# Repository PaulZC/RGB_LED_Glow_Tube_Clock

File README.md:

# RGB LED Glow Tube Clock

A drop-in replacement PCB for one of the popular LED "Nixie" Glow Tube Clocks available through the usual suppliers.

Features:

* ESP32 WROOM processor - uses WiFi to obtain network time from an NTP server
* 60 x WS2812-2020 2mm x 2mm RGB LEDs - to illuminate the engraved acrylic glow tube digits
* VEML7700 ambient light (lux) sensor - the lux can be used to adjust the LED brightness
* USB-C interface - for 5V power and firmware updates

Enjoy!

**_Paul_**

## Licence

Please see [LICENSE.md](./LICENSE.md) for details.

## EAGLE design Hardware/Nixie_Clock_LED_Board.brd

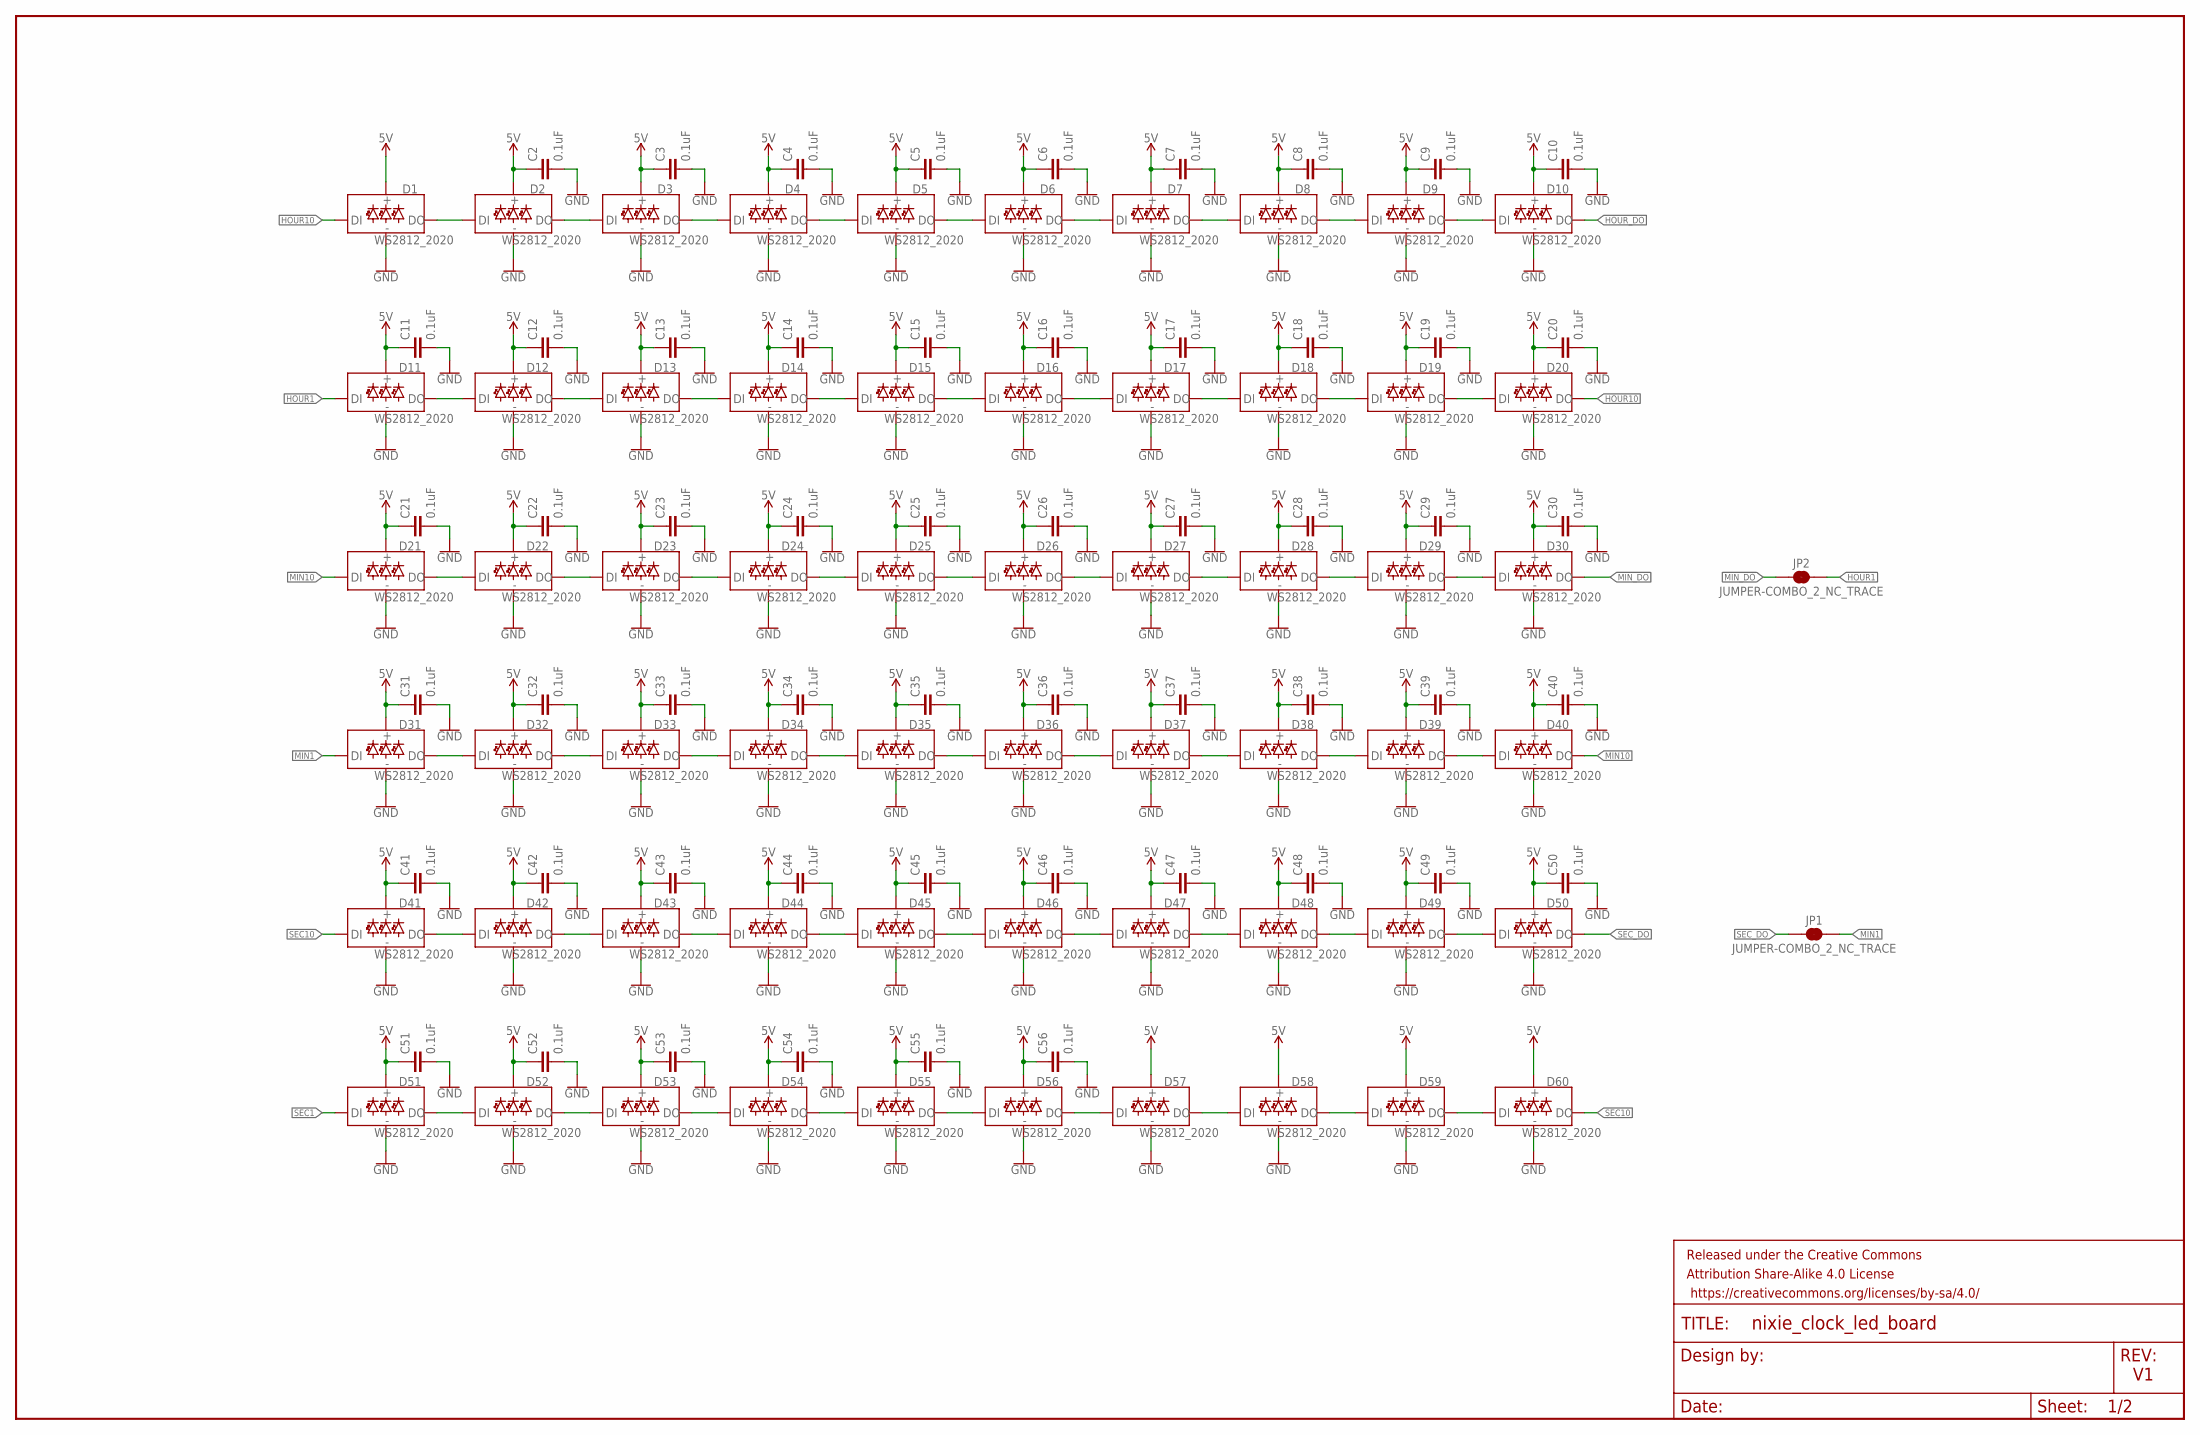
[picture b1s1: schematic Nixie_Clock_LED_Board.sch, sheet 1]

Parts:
C2, C3, C4, C5, C6, C7, C8, C9, C10, C11, C12, C13, C14, C15, C16, C17, C18, C19, C20, C21, C22, C23, C24, C25, C26, C27, C28, C29, C30, C31, C32, C33, C34, C35, C36, C37, C38, C39, C40, C41, C42, C43, C44, C45, C46, C47, C48, C49, C50, C51, C52, C53, C54, C55, C56: 0.1uF; 0603
D1, D2, D3, D4, D5, D6, D7, D8, D9, D10, D11, D12, D13, D14, D15, D16, D17, D18, D19, D20, D21, D22, D23, D24, D25, D26, D27, D28, D29, D30, D31, D32, D33, D34, D35, D36, D37, D38, D39, D40, D41, D42, D43, D44, D45, D46, D47, D48, D49, D50, D51, D52, D53, D54, D55, D56, D57, D58, D59, D60: WS2812_2020; WS2812-2020
FRAME2: FRAME-LEDGER; CREATIVE_COMMONS
JP1, JP2: JUMPER-COMBO_2_NC_TRACE; COMBO-JUMPER_2_NC_TRACE

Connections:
5V: C2.1, C3.1, C4.1, C5.1, C6.1, C7.1, C8.1, C9.1, C10.1, C11.1, C12.1, C13.1, C14.1, C15.1, C16.1, C17.1, C18.1, C19.1, C20.1, C21.1, C22.1, C23.1, C24.1, C25.1, C26.1, C27.1, C28.1, C29.1, C30.1, C31.1, C32.1, C33.1, C34.1, C35.1, C36.1, C37.1, C38.1, C39.1, C40.1, C41.1, C42.1, C43.1, C44.1, C45.1, C46.1, C47.1, C48.1, C49.1, C50.1, C51.1, C52.1, C53.1, C54.1, C55.1, C56.1, D1.VCC, D2.VCC, D3.VCC, D4.VCC, D5.VCC, D6.VCC, D7.VCC, D8.VCC, D9.VCC, D10.VCC, D11.VCC, D12.VCC, D13.VCC, D14.VCC, D15.VCC, D16.VCC, D17.VCC, D18.VCC, D19.VCC, D20.VCC, D21.VCC, D22.VCC, D23.VCC, D24.VCC, D25.VCC, D26.VCC, D27.VCC, D28.VCC, D29.VCC, D30.VCC, D31.VCC, D32.VCC, D33.VCC, D34.VCC, D35.VCC, D36.VCC, D37.VCC, D38.VCC, D39.VCC, D40.VCC, D41.VCC, D42.VCC, D43.VCC, D44.VCC, D45.VCC, D46.VCC, D47.VCC, D48.VCC, D49.VCC, D50.VCC, D51.VCC, D52.VCC, D53.VCC, D54.VCC, D55.VCC, D56.VCC, D57.VCC, D58.VCC, D59.VCC, D60.VCC; also elsewhere on the board
GND: C2.2, C3.2, C4.2, C5.2, C6.2, C7.2, C8.2, C9.2, C10.2, C11.2, C12.2, C13.2, C14.2, C15.2, C16.2, C17.2, C18.2, C19.2, C20.2, C21.2, C22.2, C23.2, C24.2, C25.2, C26.2, C27.2, C28.2, C29.2, C30.2, C31.2, C32.2, C33.2, C34.2, C35.2, C36.2, C37.2, C38.2, C39.2, C40.2, C41.2, C42.2, C43.2, C44.2, C45.2, C46.2, C47.2, C48.2, C49.2, C50.2, C51.2, C52.2, C53.2, C54.2, C55.2, C56.2, D1.GND, D2.GND, D3.GND, D4.GND, D5.GND, D6.GND, D7.GND, D8.GND, D9.GND, D10.GND, D11.GND, D12.GND, D13.GND, D14.GND, D15.GND, D16.GND, D17.GND, D18.GND, D19.GND, D20.GND, D21.GND, D22.GND, D23.GND, D24.GND, D25.GND, D26.GND, D27.GND, D28.GND, D29.GND, D30.GND, D31.GND, D32.GND, D33.GND, D34.GND, D35.GND, D36.GND, D37.GND, D38.GND, D39.GND, D40.GND, D41.GND, D42.GND, D43.GND, D44.GND, D45.GND, D46.GND, D47.GND, D48.GND, D49.GND, D50.GND, D51.GND, D52.GND, D53.GND, D54.GND, D55.GND, D56.GND, D57.GND, D58.GND, D59.GND, D60.GND; also elsewhere on the board
HOUR1: D11.DI, JP2.2, JP2.4 (2); also elsewhere on the board
HOUR10: D1.DI, D20.DO
HOUR_DO: D10.DO
MIN1: D31.DI, JP1.2, JP1.4 (2); also elsewhere on the board
MIN10: D21.DI, D40.DO
MIN_DO: D30.DO, JP2.1, JP2.3 (1)
unnamed: D1.DO, D2.DI
unnamed: D2.DO, D3.DI
unnamed: D3.DO, D4.DI
unnamed: D4.DO, D5.DI
unnamed: D5.DO, D6.DI
unnamed: D6.DO, D7.DI
unnamed: D7.DO, D8.DI
unnamed: D8.DO, D9.DI
unnamed: D9.DO, D10.DI
unnamed: D11.DO, D12.DI
unnamed: D12.DO, D13.DI
unnamed: D13.DO, D14.DI
unnamed: D14.DO, D15.DI
unnamed: D15.DO, D16.DI
unnamed: D16.DO, D17.DI
unnamed: D17.DO, D18.DI
unnamed: D18.DO, D19.DI
unnamed: D19.DO, D20.DI
unnamed: D41.DO, D42.DI
unnamed: D21.DO, D22.DI
unnamed: D22.DO, D23.DI
unnamed: D23.DO, D24.DI
unnamed: D24.DO, D25.DI
unnamed: D25.DO, D26.DI
unnamed: D26.DO, D27.DI
unnamed: D27.DO, D28.DI
unnamed: D28.DO, D29.DI
unnamed: D29.DO, D30.DI
unnamed: D31.DO, D32.DI
unnamed: D32.DO, D33.DI
unnamed: D33.DO, D34.DI
unnamed: D34.DO, D35.DI
unnamed: D35.DO, D36.DI
unnamed: D36.DO, D37.DI
unnamed: D37.DO, D38.DI
unnamed: D38.DO, D39.DI
unnamed: D39.DO, D40.DI
unnamed: D42.DO, D43.DI
unnamed: D43.DO, D44.DI
unnamed: D44.DO, D45.DI
unnamed: D45.DO, D46.DI
unnamed: D46.DO, D47.DI
unnamed: D47.DO, D48.DI
unnamed: D48.DO, D49.DI
unnamed: D49.DO, D50.DI
unnamed: D51.DO, D52.DI
unnamed: D52.DO, D53.DI
unnamed: D53.DO, D54.DI
unnamed: D54.DO, D55.DI
unnamed: D55.DO, D56.DI
unnamed: D56.DO, D57.DI
unnamed: D57.DO, D58.DI
unnamed: D58.DO, D59.DI
unnamed: D59.DO, D60.DI
SEC1: D51.DI; also elsewhere on the board
SEC10: D41.DI, D60.DO
SEC_DO: D50.DO, JP1.1, JP1.3 (1)

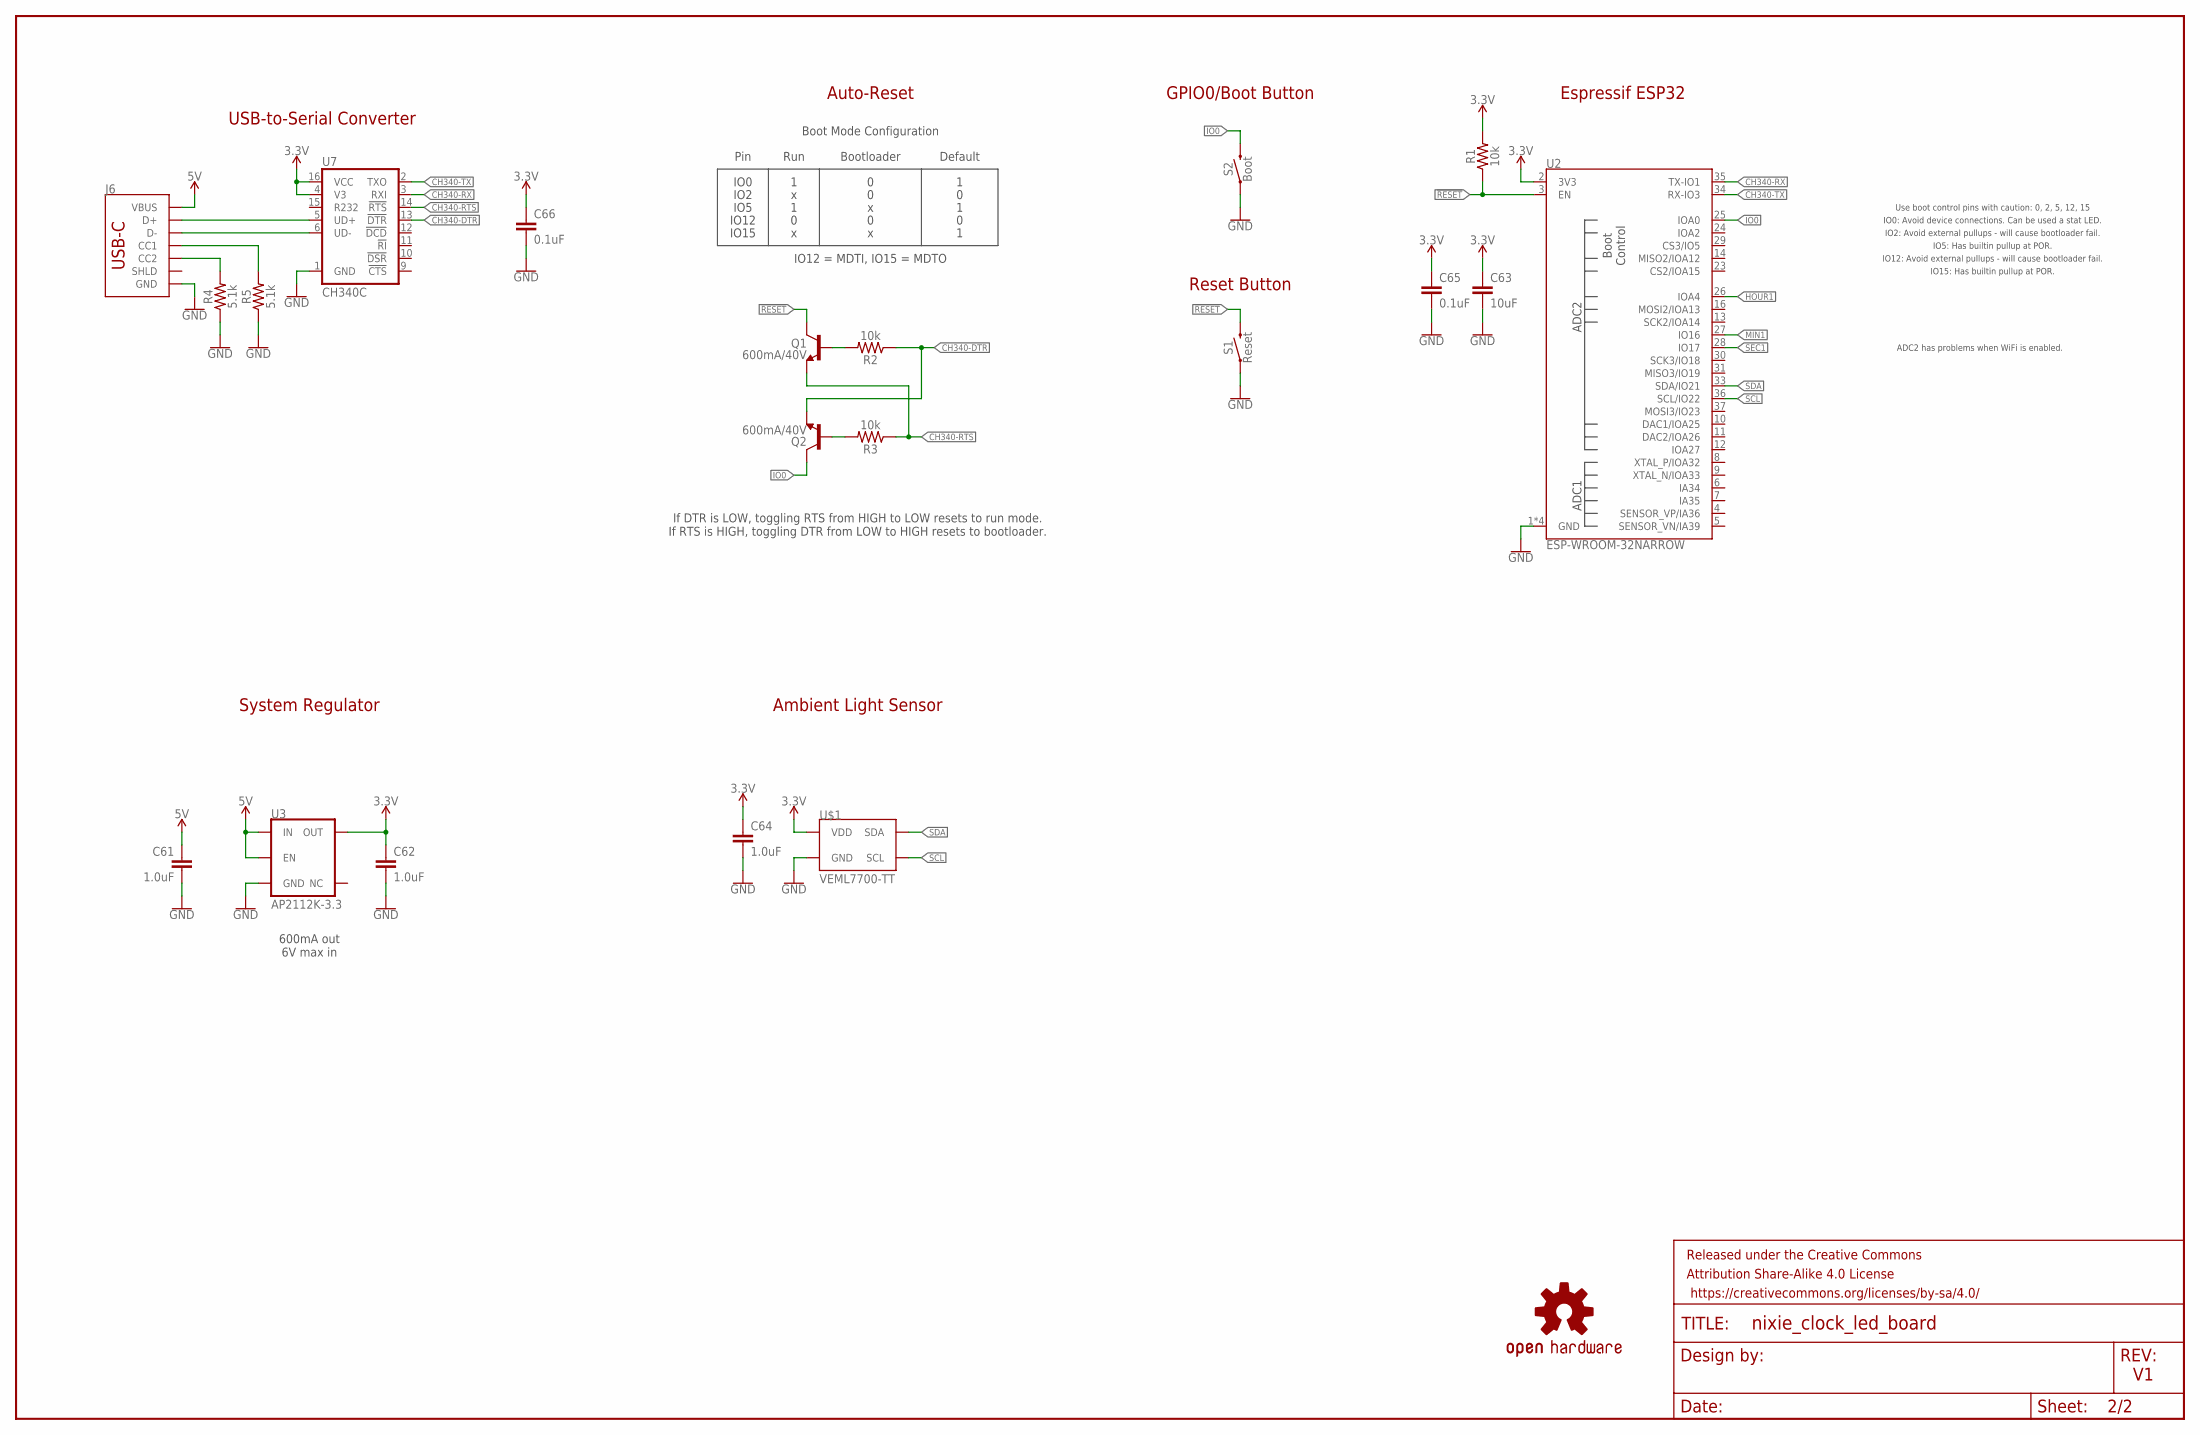
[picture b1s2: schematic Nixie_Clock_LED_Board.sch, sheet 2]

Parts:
C61, C62, C64: 1.0uF; 0603
C63: 10uF; 0603
C65, C66: 0.1uF; 0603
FRAME1: FRAME-LEDGER; CREATIVE_COMMONS
J6: USB_C_2-LAYER_PADS; USB-C-16P-2LAYER-PADS
LOGO2: OSHW-LOGOL; OSHW-LOGO-L
Q1, Q2: 600mA/40V; SOT23-3
R1, R2, R3: 10k; 0603
R4, R5: 5.1k; 0603
S1: Reset; TACTILE_SWITCH_SMD_5.2MM
S2: Boot; TACTILE_SWITCH_SMD_5.2MM
U2: ESP-WROOM-32NARROW; ESP-WROOM-32-NARROW
U3: AP2112K-3.3; SOT23-5
U7: CH340C; SO016
U$1: VEML7700-TT; VEML7700_TT

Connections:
3.3V: C62.1, C63.1, C64.1, C65.1, C66.1, R1.2, U2.2 (3V3), U3.5 (OUT), U7.4 (V3), U7.16 (VCC), U$1.2 (VDD)
5V: C61.1, J6.VBUS1 (VBUS), J6.VBUS2 (VBUS), U3.1 (IN), U3.3 (EN); also elsewhere on the board
!RESET!: Q1.3 (C), R1.1, S1.3 (2), U2.3 (EN)
CH340-DTR: Q2.2 (E), R2.1, U7.13 (!DTR)
CH340-RTS: Q1.2 (E), R3.1, U7.14 (!RTS)
CH340-RX: U2.35 (TX-IO1), U7.3 (RXI)
CH340-TX: U2.34 (RX-IO3), U7.2 (TXO)
D+: J6.A6 (D+), J6.B6 (D+), U7.5 (UD+)
D-: J6.A7 (D-), J6.B7 (D-), U7.6 (UD-)
GND: C61.2, C62.2, C63.2, C64.2, C65.2, C66.2, J6.GND, J6.GND2 (GND), R4.1, R5.1, S1.1, S2.1, U2.1 (GND), U2.15 (GND), U2.38 (GND), U2.GND, U3.2 (GND), U7.1 (GND), U$1.3 (GND); also elsewhere on the board
HOUR1: U2.26 (IOA4); also elsewhere on the board
IO0: Q2.3 (C), S2.3 (2), U2.25 (IOA0)
MIN1: U2.27 (IO16); also elsewhere on the board
unnamed: Q2.1 (B), R3.2
unnamed: Q1.1 (B), R2.2
unnamed: J6.B5 (CC2), R4.2
unnamed: J6.A5 (CC1), R5.2
SCL: U2.36 (SCL/IO22), U$1.1 (SCL)
SDA: U2.33 (SDA/IO21), U$1.4 (SDA)
SEC1: U2.28 (IO17); also elsewhere on the board

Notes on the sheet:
USB-to-Serial Converter
System Regulator
600mA out 6V max in
Auto-Reset
Espressif ESP32
Reset Button
If DTR is LOW, toggling RTS from HIGH to LOW resets to run mode. If RTS is HIGH, toggling DTR from LOW to HIGH resets to bootloader.
GPIO0/Boot Button
Pin
IO0
IO2
IO12
IO15
IO5
Run
Bootloader
Default
IO12 = MDTI, IO15 = MDTO
Boot Mode Configuration
IO0: Avoid device connections. Can be used a stat LED.
ADC2 has problems when WiFi is enabled.
IO12: Avoid external pullups - will cause bootloader fail.
Use boot control pins with caution: 0, 2, 5, 12, 15
IO2: Avoid external pullups - will cause bootloader fail.
IO15: Has builtin pullup at POR.
IO5: Has builtin pullup at POR.
Ambient Light Sensor

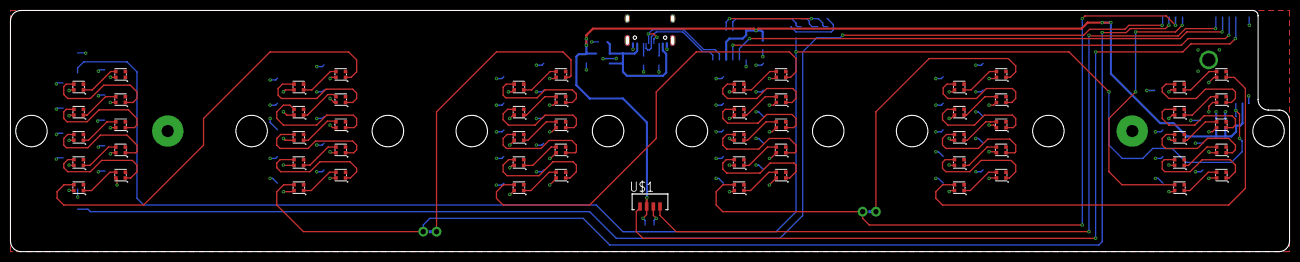
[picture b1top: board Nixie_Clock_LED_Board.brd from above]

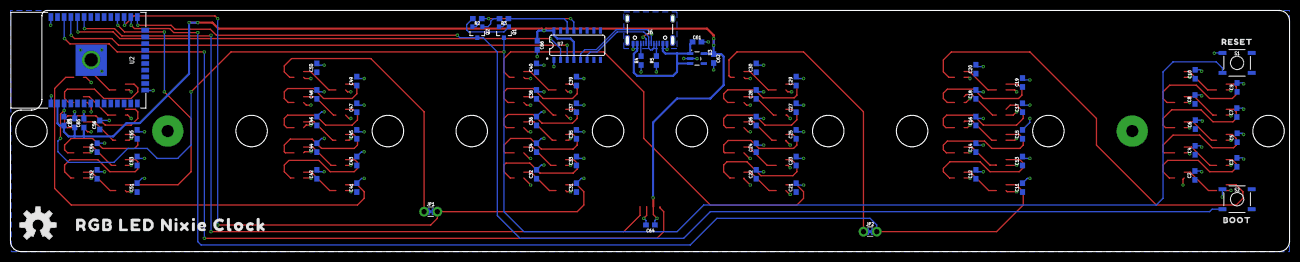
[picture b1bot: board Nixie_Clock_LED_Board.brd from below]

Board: 2 copper layers, 244.0 x 46.0 mm, 143 parts (80 on the bottom side), 79 nets.

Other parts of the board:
U$2: RESET0
U$3: BOOT0
U$4: RGB_LED_NIXIE_CLOCK0

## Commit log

2021-11-27 Add Examples 1 & 2
2021-11-27 Update examples
2021-12-12 Add example 3 - use the lux to adjust the LED brightness
2021-12-12 Add README and PCB dimensions
2021-12-12 Add schematic and PCB images
2022-07-05 Add RGB_Nixie_Clock_Test_4 - uses SNTP and Time Zone Rule
2022-10-01 Update license info

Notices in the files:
parts and their libraries:
SparkFun-Aesthetics: Licensing: Creative Commons ShareAlike 4.0 International - https://creativecommons.org/licenses/by-sa/4.0
SparkFun-Aesthetics: Released under the Creative Commons Attribution Share-Alike 4.0 License
SparkFun-Aesthetics: https://creativecommons.org/licenses/by-sa/4.0
